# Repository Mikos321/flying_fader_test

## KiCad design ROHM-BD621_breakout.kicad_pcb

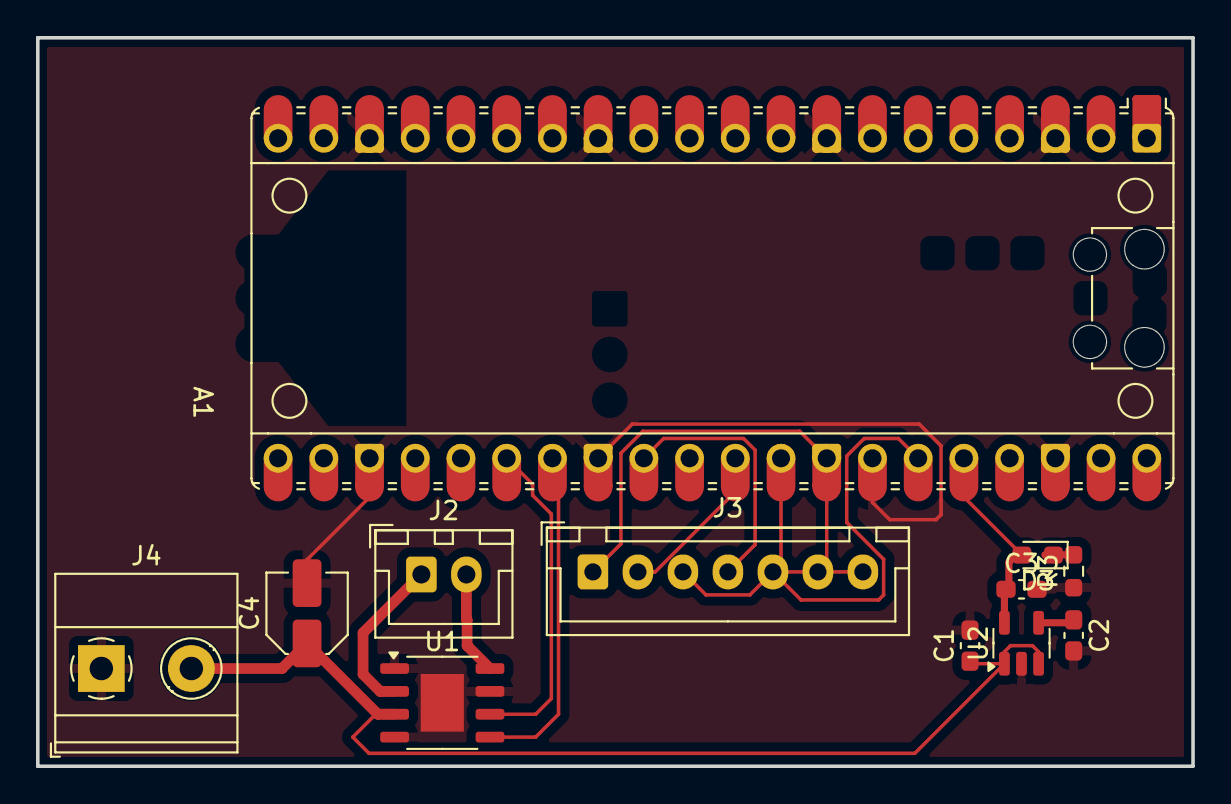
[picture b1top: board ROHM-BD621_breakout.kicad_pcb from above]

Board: 2 copper layers, 64.2 x 40.5 mm, 12 parts (0 on the bottom side), 14 nets.

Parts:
A1: RaspberryPi_Pico_W; RaspberryPi_Pico_Common
C1, C3: C; C_0603_1608Metric_Pad1.08x0.95mm_HandSolder
C2: 10nF; C_0603_1608Metric_Pad1.08x0.95mm_HandSolder
C4: C; C_Elec_4x5.4
D3: LED; LED_0603_1608Metric_Pad1.05x0.95mm_HandSolder
J2: Conn_01x02_Socket; JST_XH_B2B-XH-A_1x02_P2.50mm_Vertical
J3: Conn_01x07_Socket; JST_XH_B7B-XH-A_1x07_P2.50mm_Vertical
J4: Barrel_Jack; TerminalBlock_Phoenix_MKDS-1,5-2_1x02_P5.00mm_Horizontal
R3: R; R_0603_1608Metric_Pad0.98x0.95mm_HandSolder
U1: HTSOP-8-1EP_3.9x4.9mm_P1.27mm_EP2.4x3.2mm
U2: LP2985-3.3; SOT-23-5

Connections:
3V3: A1.36 (3V3), C3.1, D3.2 (A), U2.5 (VOUT)
GND: A1.3 (GND), A1.8 (GND), A1.13 (GND), A1.18 (GND), A1.23 (GND), A1.28 (GND), A1.34 (GPIO28_ADC2), A1.38 (GND), C1.2, C2.2, C3.2, C4.2, J4.1, R3.1, U1.1 (GND), U1.4 (GND), U1.7 (TEST), U1.9, U2.2 (GND)
unnamed: D3.1 (K), R3.2
unnamed: C2.1, U2.4 (BP)
O1: J2.1, U1.2 (OUT1)
O2: J2.2, U1.8 (OUT2)
PWM0: A1.27 (GPIO21), U1.5 (IN1)
PWM1: A1.26 (GPIO20), U1.6 (IN2)
VCC: C1.1, C4.1, J4.2, U1.3 (VCC), U2.1 (VIN), U2.3 (ON/~OFF)
sense_pin: A1.29 (GPIO22), J3.4
track+: A1.35 (ADC_VREF), J3.3, J3.5
track-: A1.33 (AGND), J3.1, J3.7
track_0: A1.31 (GPIO26_ADC0), J3.2
track_1: A1.32 (GPIO27_ADC1), J3.6
